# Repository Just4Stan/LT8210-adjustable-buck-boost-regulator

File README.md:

# LT8210 adjustable buck boost regulator

Designed in Kicad, simulated in LTSpice

Vin: 4-100V
Vout: 5, 9, 12, 15, 20, 24V
Iout: 10A (adjustable current limiting)

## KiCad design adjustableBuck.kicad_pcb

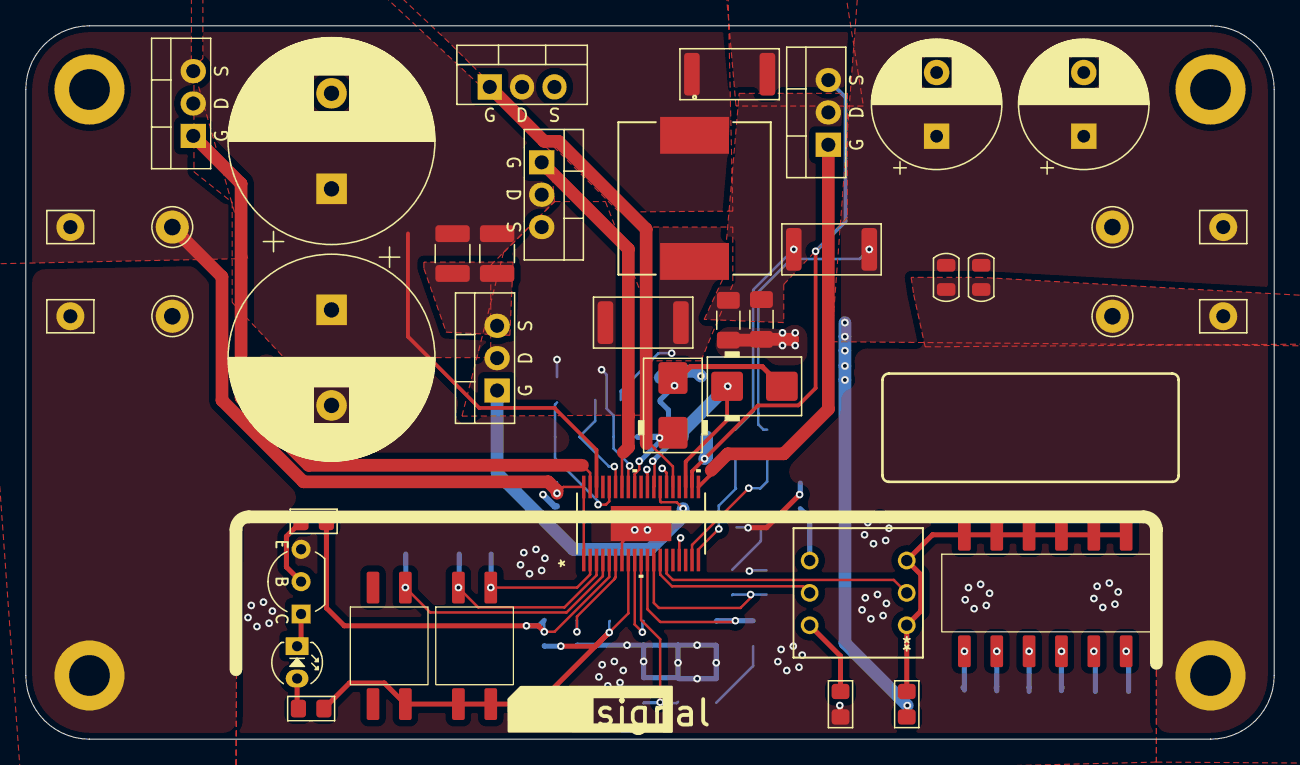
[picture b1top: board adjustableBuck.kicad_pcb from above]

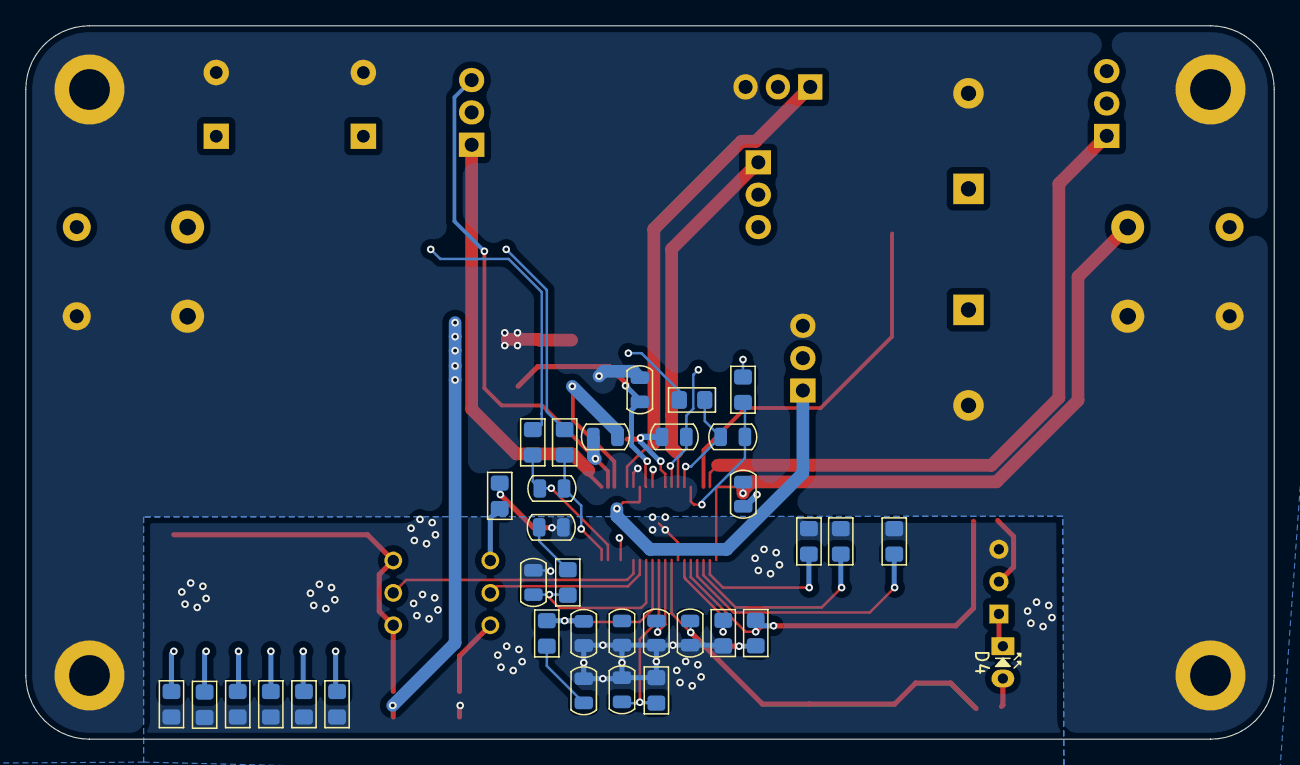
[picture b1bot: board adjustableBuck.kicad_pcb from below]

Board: 4 copper layers, 98.0 x 56.0 mm, 77 parts (33 on the bottom side), 48 nets.

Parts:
C1: 1uF 100v; C_0805_2012Metric
C4, C13: 22uF 35V; C_1206_3216Metric_Pad1.33x1.80mm_HandSolder
C5, C7: 220uF 100V; CP_Radial_D16.0mm_P7.50mm
C8, C9: 10uF 100V; C_1210_3225Metric_Pad1.33x2.70mm_HandSolder
C10, C12: 220nF; C_0805_2012Metric
C11, C25, C26: 4.7uF 35v; C_0805_2012Metric
C14, C15: 470uF 35V; CP_Radial_D10.0mm_P5.00mm
C16: 2.2uF; C_0805_2012Metric
C17: 22nF; C_0805_2012Metric
C18: 820pF; C_0805_2012Metric
C19: 6.8nF; C_0805_2012Metric
C20: 2.2nF; C_0805_2012Metric
C21, C22: 1nF; C_0805_2012Metric
C23, C24, C27: 220pF; C_0805_2012Metric
D2, D3: MURS160; D_SMB
D4: LED; LED_D3.0mm
H1, H2, H3, H4: MountingHole_Pad; MountingHole_3.2mm_M3_ISO14580_Pad
L1: 7443320680; IND_1210-WE-HCC_WRE
Q6: BC547; TO-92_Inline_Wide_CBE
Q7, Q8, Q9, Q10, Q11: IRFB4615; TO-220-3_Vertical_GDS
R1, R5: 5mOhm; R_2512_6332Metric
R2: solderBridge; R_2512_6332Metric
R6, R7: 10R; R_0805_2012Metric_Pad1.20x1.40mm_HandSolder
R8, R9: 49.9R; R_0805_2012Metric_Pad1.20x1.40mm_HandSolder
R10, R16, R18, R35, R36: 10k; R_0805_2012Metric_Pad1.20x1.40mm_HandSolder
R11: 1k; R_0805_2012Metric_Pad1.20x1.40mm_HandSolder
R12: 220R; R_0805_2012Metric_Pad1.20x1.40mm_HandSolder
R13: 28k; R_0805_2012Metric_Pad1.20x1.40mm_HandSolder
R14: 2.61k; R_0805_2012Metric_Pad1.20x1.40mm_HandSolder
R15: 60.4k; R_0805_2012Metric_Pad1.20x1.40mm_HandSolder
R17: 2.4k; R_0805_2012Metric_Pad1.20x1.40mm_HandSolder
R20: 1.2k; R_0805_2012Metric_Pad1.20x1.40mm_HandSolder
R21: 910R; R_0805_2012Metric_Pad1.20x1.40mm_HandSolder
R22: 750R; R_0805_2012Metric_Pad1.20x1.40mm_HandSolder
R23: 510R; R_0805_2012Metric_Pad1.20x1.40mm_HandSolder
R24: 430R; R_0805_2012Metric_Pad1.20x1.40mm_HandSolder
R25: 1.5k; R_0805_2012Metric_Pad1.20x1.40mm_HandSolder
R26: 680R; R_0805_2012Metric_Pad1.20x1.40mm_HandSolder
R33: 33k; R_0805_2012Metric_Pad1.20x1.40mm_HandSolder
SW2, SW6: DIP2; 2DIPCFS
SW3: DIP6; 6DIPCFS
SW4: 76SD01ST; SW6_76SD01ST_GHL
TP1, TP7, TP8, TP21: TestPoint; Pin_D1.3mm_L11.0mm
TP3, TP4, TP5, TP6: ProbePoint; Pin_D1.1mm_L10.2mm_W3.5mm_Flat
U1: LT8210EFE; 05-08-1772_ADI-M

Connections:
/BG1: Q9.1 (G), U1.26 (BG1)
/BG2: Q10.1 (G), U1.24 (BG2)
/BST1: C10.1, D2.1 (K), U1.30 (BST1)
/BST2: C12.1, D3.1 (K), U1.22 (BST2)
/DG: Q8.1 (G), U1.37 (DG)
/FB1: SW4.2, U1.14 (FB1)
/FB2: SW4.5, U1.13 (FB2)
/GateVcc: C11.1, D2.2 (A), D3.2 (A), U1.27 (GateVcc)
/IMON: C27.1, R33.1, U1.10 (IMON)
/MODE1: R35.1, SW2.1, U1.3 (MODE1)
/MODE2: R36.1, SW2.2, U1.2 (MODE2)
/PWGD: R10.2, R11.1, U1.5 (PWGD)
/SNSN1: C21.2, R7.2, U1.33 (SNSN1)
/SNSN2: C22.2, R9.2, U1.18 (SNSN2)
/SNSP1: C21.1, R6.1, U1.34 (SNSP1)
/SNSP2: C22.1, R8.2, U1.19 (SNSP2)
/SS: C17.2, U1.9 (SS)
/SW1: C10.2, Q7.3 (S), Q9.2 (D), R1.1, R6.2, U1.31 (SW1)
/SW2: C12.2, Q11.3 (S), R2.2, U1.21 (SW2)
/TG1: Q7.1 (G), U1.32 (TG1)
/TG2: Q11.1 (G), U1.20 (TG2)
/VC1: C18.2, R14.2, U1.11 (VC1)
/VC2: C23.2, R15.2, U1.12 (VC2)
/Vin: C1.1, Q8.3 (S), TP3.1, TP7.1, U1.1 (EN/UVLO), U1.38 (Vin)
/VinP: C5.1, C7.1, C8.1, C9.1, Q7.2 (D), Q8.2 (D), U1.36 (VinP)
/Vout: C14.1, C15.1, C25.1, C26.1, R5.2, R9.1, R16.1, TP5.1, TP8.1, U1.16 (VOUT), U1.28 (ExtVcc)
/manual_bus: R16.2, SW3.1, SW3.2, SW3.3, SW3.4, SW3.5, SW3.6, SW4.1, SW4.3
GNDPWR: C1.2, C4.2, C5.2, C7.2, C8.2, C9.2, C11.2, C13.2, C14.2, C15.2, C25.2, C26.2, H1.1, H2.1, H3.1, H4.1, Q9.3 (S), Q10.3 (S), TP1.1, TP4.1, TP6.1, TP21.1, U1.25 (PGND)
GNDS: C16.2, C17.1, C18.1, C19.1, C20.1, C23.1, C24.1, C27.2, Q6.3 (E), R13.1, R17.2, R18.1, R20.2, R21.2, R22.2, R23.2, R24.2, R25.2, R26.2, R33.2, R35.2, R36.2, U1.7 (GND), U1.39 (SGND)
unnamed: C19.2, R14.1
unnamed: C20.2, R15.1
unnamed: D4.2 (A), R12.1
unnamed: D4.1 (K), Q6.1 (C)
unnamed: L1.2, R1.2, R7.1
unnamed: Q6.2 (B), R11.2
unnamed: L1.1, Q10.2 (D), R2.1
unnamed: C4.1, C13.1, Q11.2 (D), R5.1, R8.1
unnamed: R17.1, SW3.12
unnamed: R20.1, SW3.11
unnamed: R21.1, SW3.10
unnamed: R22.1, SW3.9
unnamed: R23.1, SW3.8
unnamed: R24.1, SW3.7
unnamed: R25.1, SW4.4
unnamed: R26.1, SW4.6
unnamed: R13.2, U1.6 (RT)
unnamed: R18.2, SW6.2, U1.4 (SYNC/SPRD)
VDD: C16.1, R10.1, R12.2, SW2.3, SW2.4, SW6.3, U1.8 (VDD)

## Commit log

2025-11-01 First schematic rev
2025-11-01 Update README with design and specifications
    Added specifications and design details for the LT8210 regulator.
2025-11-01 First board layout
2025-11-10 semi final design and pcb layout
2025-11-10 added local libraries
2026-02-24 Add images to README for LT8210 regulator
    Added images to the README for better visualization.
